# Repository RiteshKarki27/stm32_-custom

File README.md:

This is a custom designed board which includes an STM32 controller with common serial communication modules like I2C, UART, SPI, CAN and USB.

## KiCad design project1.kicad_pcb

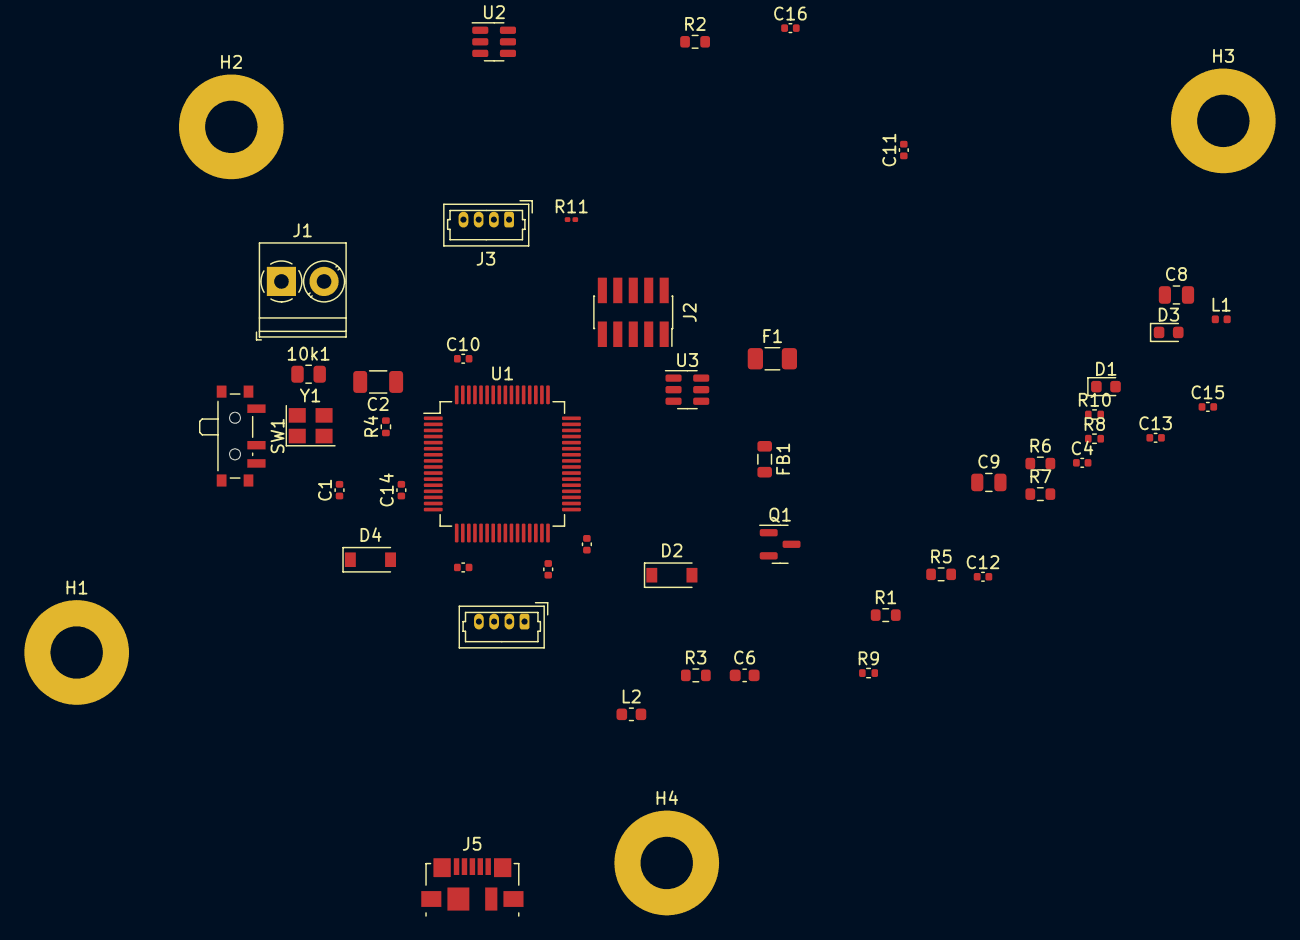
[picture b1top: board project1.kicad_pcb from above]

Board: 4 copper layers, 51 parts (0 on the bottom side), 36 nets, no tracks yet.

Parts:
10k1: R; R_0805_2012Metric
C1, C4: 12p; C_0402_1005Metric
C2: 4u7; C_1206_3216Metric
C3, C5, C7, C10, C11: 100n; C_0402_1005Metric
C6: 2u2; C_0603_1608Metric
C8: 2u2; C_0805_2012Metric
C9: 10u; C_0805_2012Metric
C12: 1u; C_0402_1005Metric
C13, C14, C15, C16: 10n; C_0402_1005Metric
D1, D3: BLUE; LED_0603_1608Metric
D2: D_Schottky; D_SOD-123
D4: B5819W; D_SOD-123
F1: 250mA; Fuse_1206_3216Metric
FB1: 600 @ 600MHz; L_0805_2012Metric
H1, H2, H3, H4: MountingHole_Pad; MountingHole_4.3mm_M4_Pad
J1: Screw_Terminal_01x02; TerminalBlock_Phoenix_PT-1,5-2-3.5-H_1x02_P3.50mm_Horizontal
J2: SWD; PinSocket_2x05_P1.27mm_Vertical_SMD
J3: I2C; Molex_PicoBlade_53047-0410_1x04_P1.25mm_Vertical
J4: UART; Molex_PicoBlade_53047-0410_1x04_P1.25mm_Vertical
J5: USB_B_Micro; USB_Micro-B_Molex_47346-0001
L1: 39n; L_0402_1005Metric
L2: 4u7; L_0603_1608Metric
Q1: AO3401A; SOT-23
R1: 1k5; R_0603_1608Metric
R2: 100k; R_0603_1608Metric
R3: 68k; R_0603_1608Metric
R4: 47; R_0402_1005Metric
R5: 47k; R_0603_1608Metric
R6: 15k; R_0603_1608Metric
R7: 270; R_0603_1608Metric
R8, R10: 2K2; R_0402_1005Metric
R9: 1k5; R_0402_1005Metric
R11: 22; R_0201_0603Metric
SW1: SW_SPDT; SW_SPDT_PCM12
U1: STM32F405RGTx; LQFP-64_10x10mm_P0.5mm
U2: MP2359DJ-LF-Z; SOT-23-6
U3: USBLC6-2SC6; SOT-23-6
Y1: 16MHz; Crystal_SMD_3225-4Pin_3.2x2.5mm

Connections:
+3.3V: C2.1, C3.1, C5.1, C7.1, C10.1, C11.1, C15.2, C16.2, D3.2 (A), J2.1, J3.1, J4.1, L1.1, L2.2, R5.1, R8.1, R10.1, SW1.1 (A), U1.1 (VBAT), U1.19 (VDD), U1.32 (VDD), U1.48 (VDD), U1.64 (VDD)
+3.3VA: C12.1, C14.1, L1.2, U1.13 (VDDA)
+5V: D2.2 (A), J5.1 (VBUS), U3.5 (VBUS)
+12V: F1.1, J1.1
BOOT0: 10k1.2, U1.60 (BOOT0)
BUCK_BST: C13.1, U2.1 (BST)
BUCK_EN: R2.2, R3.1, U2.4 (EN)
BUCK_FB: R5.2, R6.1, U2.3 (FB)
BUCK_IN: C9.1, FB1.1, R2.1, U2.5 (IN)
BUCK_SW: C13.2, D4.1 (K), L2.1, U2.6 (SW)
GND: C1.2, C2.2, C3.2, C4.2, C5.2, C6.2, C7.2, C8.2, C9.2, C10.2, C11.2, C12.2, C14.2, C15.1, C16.1, D4.2 (A), H1.1, H2.1, H3.1, H4.1, J1.2, J2.3, J2.5, J2.9, J3.4, J4.4, J5.5 (GND), Q1.1 (G), R1.2, R3.2, R7.2, R9.2, SW1.3 (C), U1.12 (VSSA), U1.18 (VSS), U1.63 (VSS), U2.2 (GND), U3.2 (GND), Y1.2, Y1.4
HSE_IN: C1.1, U1.5 (PH0), Y1.1
HSE_OUT: R4.1, U1.6 (PH1)
I2C1_SCL: J3.2, R8.2, U1.58 (PB6)
I2C1_SDA: J3.3, R10.2, U1.59 (PB7)
LED_STATUS: D1.2 (A), U1.16 (PA2)
NRST: J2.10, U1.7 (NRST)
unnamed: 10k1.1, SW1.2 (B)
unnamed: C4.1, R4.2, Y1.3
unnamed: C6.1, U1.31 (VCAP_1)
unnamed: C8.1, U1.47 (VCAP_2)
unnamed: D1.1 (K), R1.1
unnamed: D2.1 (K), FB1.2, Q1.2 (S)
unnamed: D3.1 (K), R9.1
unnamed: F1.2, Q1.3 (D)
unnamed: J2.2, R11.1
unnamed: R6.2, R7.1
SWCLK: J2.4, U1.49 (PA14)
SWDIO: R11.2, U1.46 (PA13)
SWO: J2.6, U1.55 (PB3)
UART3_RX: J4.3, U1.30 (PB11)
UART3_TX: J4.2, U1.29 (PB10)
USB_CONN_D+: J5.3 (D+), U3.3 (I/O2)
USB_CONN_D-: J5.2 (D-), U3.1 (I/O1)
USB_D+: U1.45 (PA12), U3.4 (I/O2)
USB_D-: U1.44 (PA11), U3.6 (I/O1)

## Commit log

2023-01-18 first message
2023-03-02 Created README.md
